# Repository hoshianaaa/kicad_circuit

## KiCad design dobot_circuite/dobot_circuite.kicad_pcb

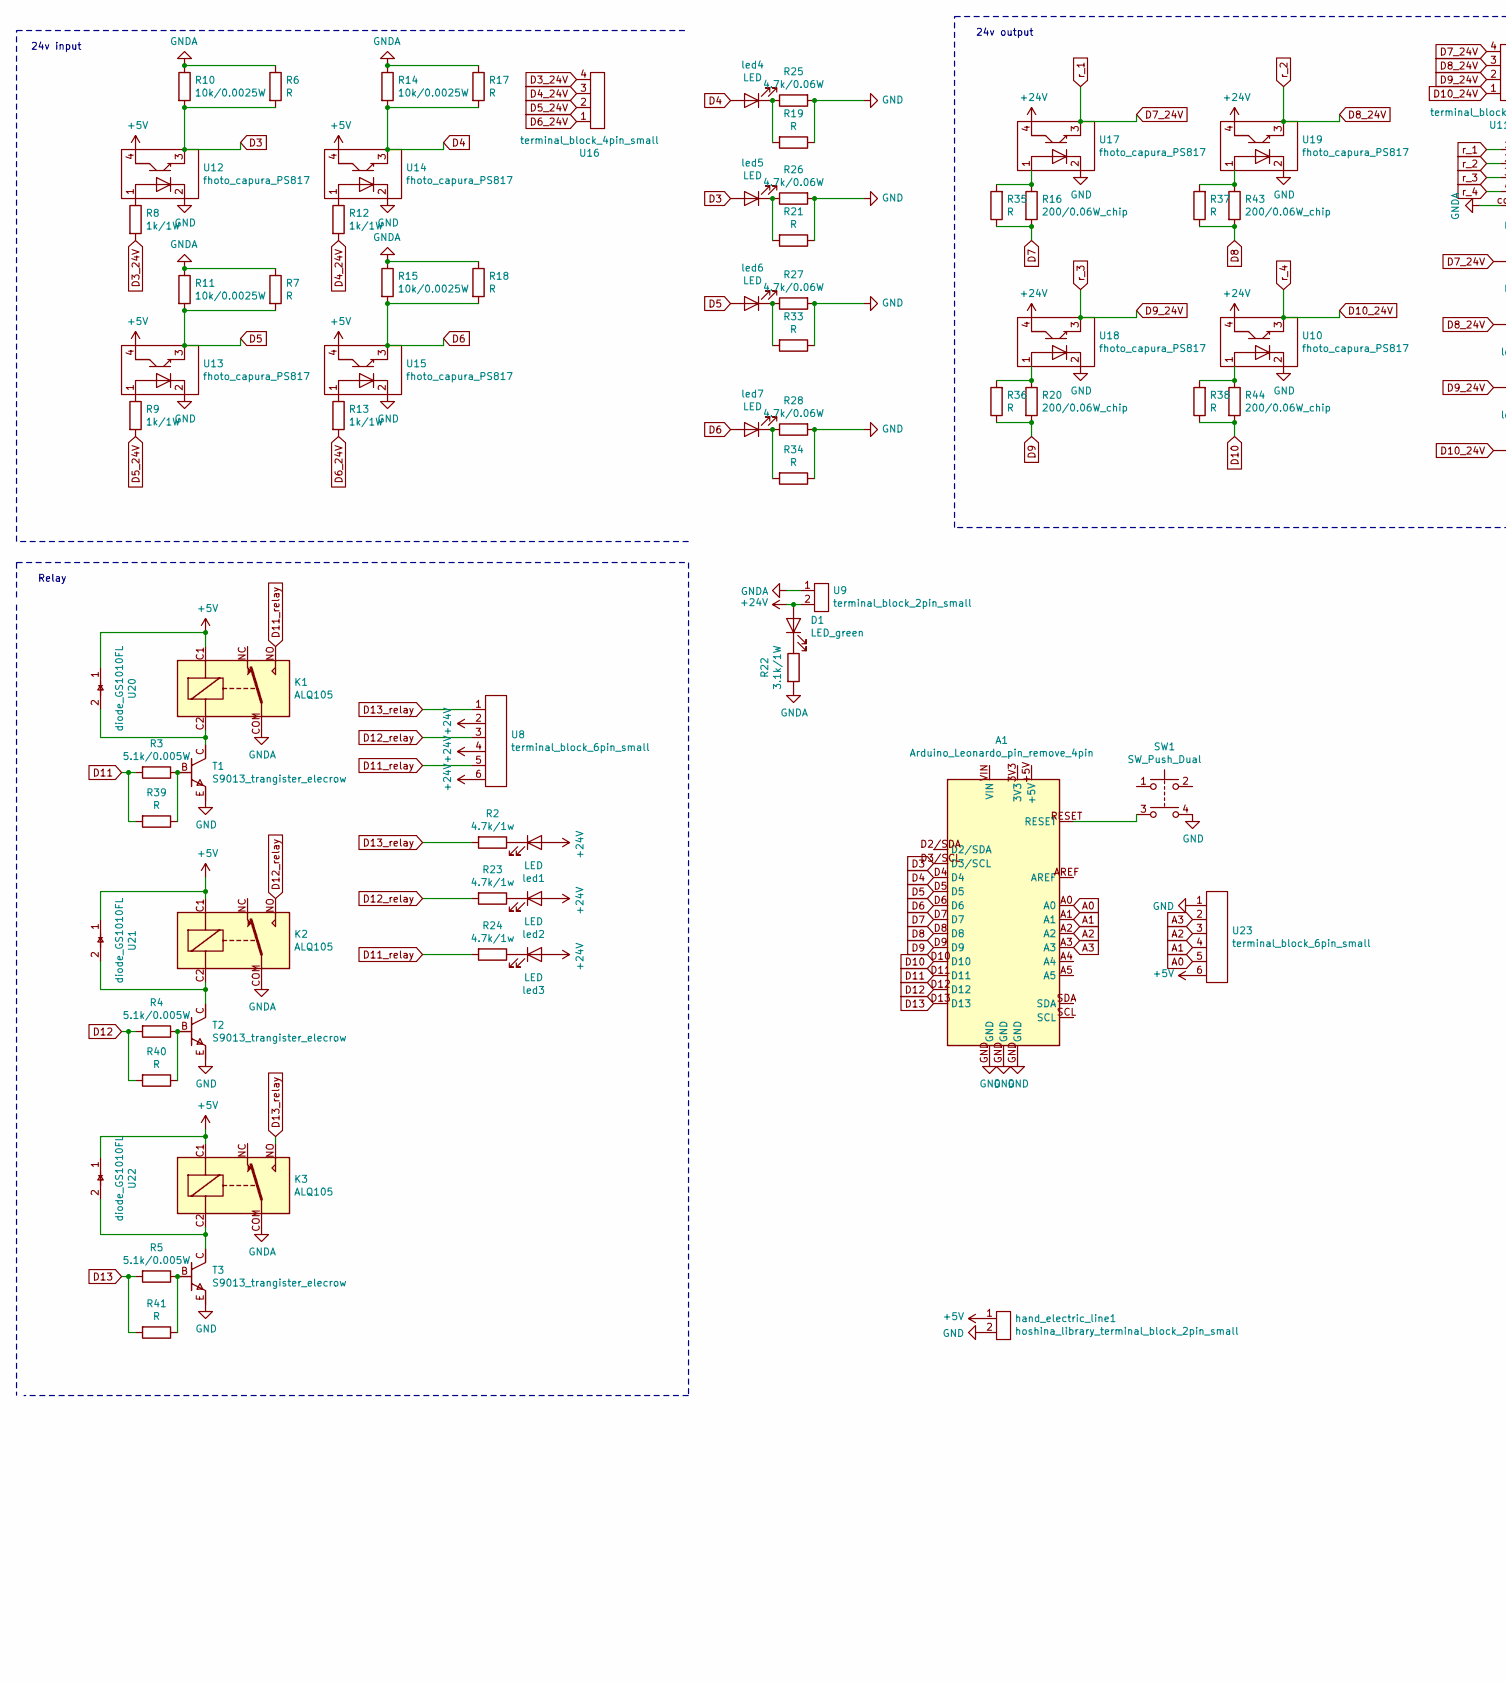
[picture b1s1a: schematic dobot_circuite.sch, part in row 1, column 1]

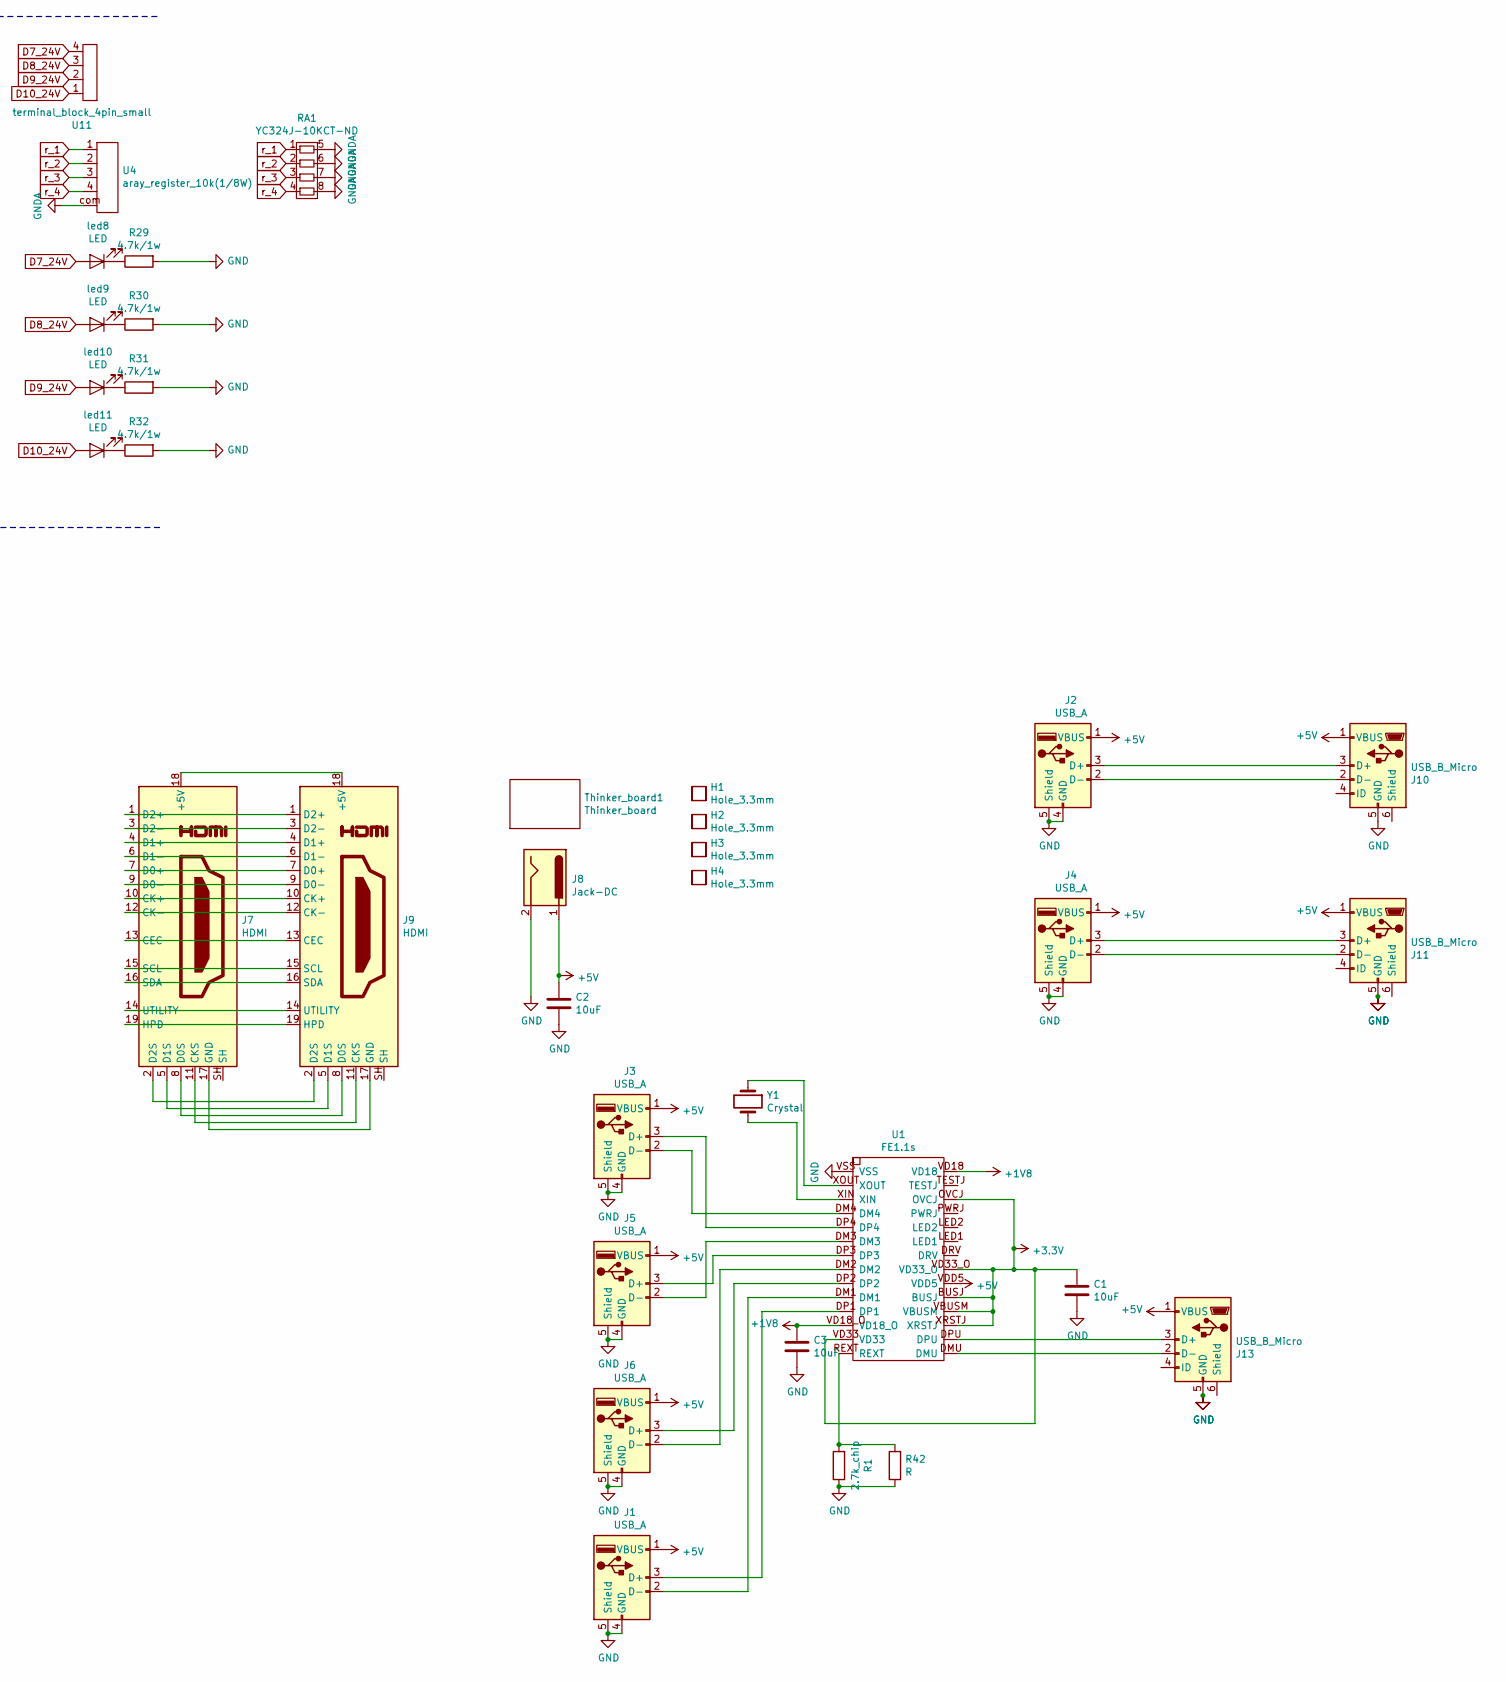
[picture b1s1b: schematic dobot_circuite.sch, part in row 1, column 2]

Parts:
A1: Arduino_Leonardo_pin_remove_4pin; arduino_leonard_remove_4pin
C1, C2, C3: 10uF; capa1608
D1: LED_green; LED_1608
H1, H2, H3, H4: Hole_3.3mm
J1, J2, J3, J4, J5, J6: USB_A; USB-A1
J7, J9: HDMI; HDMI_2000-1-1-20-00-BK
J8: Jack-DC; BarrelJack_Horizontal
J10, J11, J13: USB_B_Micro; USB_Micro-B_Molex_47346-0001
K1, K2, K3: ALQ105; ALQ105_akituki
R1: 2.7k_chip; register_0603
R2, R23, R24, R29, R30, R31, R32: 4.7k/1w; carbon_register
R3, R4, R5: 5.1k/0.005W; register_0603
R6, R7, R17, R18, R19, R21, R33, R34, R35, R36, R37, R38, R39, R40, R41, R42: R; carbon_register_1_6W_
R8, R9, R12, R13: 1k/1W; carbon_register
R10, R11, R14, R15: 10k/0.0025W; register_0603
R16, R20, R43, R44: 200/0.06W_chip; register_0603
R22: 3.1k/1W; carbon_register
R25, R26, R27, R28: 4.7k/0.06W; register_0603
RA1: YC324J-10KCT-ND
SW1: SW_Push_Dual; SW_TH_Tactile_Omron_B3F-10xx
T1, T2, T3: S9013_trangister_elecrow; S9013
Thinker_board1: Thinker_board
U1: FE1.1s
U4: aray_register_10k(1/8W); array_register
U8, U23: terminal_block_6pin_small
U9: terminal_block_2pin_small
U10, U12, U13, U14, U15, U17, U18, U19: fhoto_capura_PS817; fhoto_capra_PS817
U11, U16: terminal_block_4pin_small
U20, U21, U22: diode_GS1010FL
Y1: Crystal; Crystal_SMD_5032-2Pin_5.0x3.2mm
hand_electric_line1: hoshina_library_terminal_block_2pin_small; XH2_pin
led1, led2, led3, led4, led5, led6, led7, led8, led9, led10, led11: LED; LED_1608

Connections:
+1V8: C3.1, U1.VD18, U1.VD18_O
+3V3: C1.1, U1.BUSJ, U1.OVCJ, U1.VBUSM, U1.VD33, U1.VD33_O, U1.XRSTJ
+5V: C2.1, J1.1 (VBUS), J2.1 (VBUS), J3.1 (VBUS), J4.1 (VBUS), J5.1 (VBUS), J6.1 (VBUS), J8.1, J10.1 (VBUS), J11.1 (VBUS), J13.1 (VBUS), K1.C1, K2.C1, K3.C1, U1.VDD5, U12.4, U13.4, U14.4, U15.4, U20.1, U21.1, U22.1, U23.6, hand_electric_line1.1
+24V: D1.2 (A), U8.2, U8.4, U8.6, U9.2, U10.4, U17.4, U18.4, U19.4, led1.2 (A), led2.2 (A), led3.2 (A)
A0: A1.A0, U23.5
A1: A1.A1, U23.4
A2: A1.A2, U23.3
A3: A1.A3, U23.2
D3: A1.D3/SCL, R6.2, R10.2, U12.3, led5.2 (A)
D3_24V: R8.2, U16.4
D4: A1.D4, R14.2, R17.2, U14.3, led4.2 (A)
D4_24V: R12.2, U16.3
D5: A1.D5, R7.2, R11.2, U13.3, led6.2 (A)
D5_24V: R9.2, U16.2
D6: A1.D6, R15.2, R18.2, U15.3, led7.2 (A)
D6_24V: R13.2, U16.1
D7: A1.D7, R16.2, R35.1
D7_24V: RA1.1, U4.1, U11.4, U17.3, led8.2 (A)
D8: A1.D8, R37.1, R43.2
D8_24V: RA1.2, U4.2, U11.3, U19.3, led9.2 (A)
D9: A1.D9, R20.2, R36.1
D9_24V: RA1.3, U4.3, U11.2, U18.3, led10.2 (A)
D10: A1.D10, R38.1, R44.2
D10_24V: RA1.4, U4.4, U10.3, U11.1, led11.2 (A)
D11: A1.D11, R3.2, R39.2
D11_relay: K1.NO, R24.2, U8.5
D12: A1.D12, R4.2, R40.2
D12_relay: K2.NO, R23.2, U8.3
D13: A1.D13, R5.2, R41.2
D13_relay: K3.NO, R2.2, U8.1
GND: A1.GND, C1.2, C2.2, C3.2, J1.4 (GND), J1.5 (Shield), J2.4 (GND), J2.5 (Shield), J3.4 (GND), J3.5 (Shield), J4.4 (GND), J4.5 (Shield), J5.4 (GND), J5.5 (Shield), J6.4 (GND), J6.5 (Shield), J8.2, J10.5 (GND), J11.5 (GND), J13.5 (GND), R1.1, R19.1, R21.1, R25.2, R26.2, R27.2, R28.2, R29.2, R30.2, R31.2, R32.2, R33.1, R34.1, R42.1, SW1.4, T1.E, T2.E, T3.E, U1.VSS, U10.2, U12.2, U13.2, U14.2, U15.2, U17.2, U18.2, U19.2, U23.1, hand_electric_line1.2
GNDA: K1.COM, K2.COM, K3.COM, R6.1, R7.1, R10.1, R11.1, R14.1, R15.1, R17.1, R18.1, R22.2, RA1.5, RA1.6, RA1.7, RA1.8, U4.com, U9.1
unnamed: A1.RESET, SW1.3
unnamed: D1.1 (K), R22.1
unnamed: J1.2 (D-), U1.DM1
unnamed: J1.3 (D+), U1.DP1
unnamed: J3.2 (D-), U1.DM4
unnamed: J3.3 (D+), U1.DP4
unnamed: J5.2 (D-), U1.DM3
unnamed: J5.3 (D+), U1.DP3
unnamed: J6.2 (D-), U1.DM2
unnamed: J6.3 (D+), U1.DP2
unnamed: J7.1 (D2+), J9.1 (D2+)
unnamed: J7.2 (D2S), J9.2 (D2S)
unnamed: J7.3 (D2-), J9.3 (D2-)
unnamed: J7.4 (D1+), J9.4 (D1+)
unnamed: J7.5 (D1S), J9.5 (D1S)
unnamed: J7.6 (D1-), J9.6 (D1-)
unnamed: J7.7 (D0+), J9.7 (D0+)
unnamed: J7.8 (D0S), J9.8 (D0S)
unnamed: J7.9 (D0-), J9.9 (D0-)
unnamed: J7.10 (CK+), J9.10 (CK+)
unnamed: J7.11 (CKS), J9.11 (CKS)
unnamed: J7.12 (CK-), J9.12 (CK-)
unnamed: J7.13 (CEC), J9.13 (CEC)
unnamed: J7.14 (UTILITY), J9.14 (UTILITY)
unnamed: J7.15 (SCL), J9.15 (SCL)
unnamed: J7.16 (SDA), J9.16 (SDA)
unnamed: J7.17 (GND), J9.17 (GND)
unnamed: J7.18 (+5V), J9.18 (+5V)
unnamed: J7.19 (HPD), J9.19 (HPD)
unnamed: J2.2 (D-), J10.2 (D-)
unnamed: J2.3 (D+), J10.3 (D+)
unnamed: J4.2 (D-), J11.2 (D-)
unnamed: J4.3 (D+), J11.3 (D+)
unnamed: J13.2 (D-), U1.DMU
unnamed: J13.3 (D+), U1.DPU
unnamed: K1.C2, T1.C, U20.2
unnamed: K2.C2, T2.C, U21.2
unnamed: K3.C2, T3.C, U22.2
unnamed: R1.2, R42.2, U1.REXT
unnamed: R2.1, led1.1 (K)
unnamed: R3.1, R39.1, T1.B
unnamed: R4.1, R40.1, T2.B
unnamed: R8.1, U12.1
unnamed: R9.1, U13.1
unnamed: R12.1, U14.1
unnamed: R13.1, U15.1
unnamed: R16.1, R35.2, U17.1
unnamed: R19.2, R25.1, led4.1 (K)
unnamed: R20.1, R36.2, U18.1
unnamed: R21.2, R26.1, led5.1 (K)
unnamed: R23.1, led2.1 (K)
unnamed: R24.1, led3.1 (K)
unnamed: R27.1, R33.2, led6.1 (K)
unnamed: R28.1, R34.2, led7.1 (K)
unnamed: R29.1, led8.1 (K)
unnamed: R30.1, led9.1 (K)
unnamed: R31.1, led10.1 (K)
unnamed: R32.1, led11.1 (K)
unnamed: R37.2, R43.1, U19.1
unnamed: R38.2, R44.1, U10.1
unnamed: R5.1, R41.1, T3.B
unnamed: U1.XIN, Y1.2
unnamed: U1.XOUT, Y1.1

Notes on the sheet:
24v input
24v output
Relay

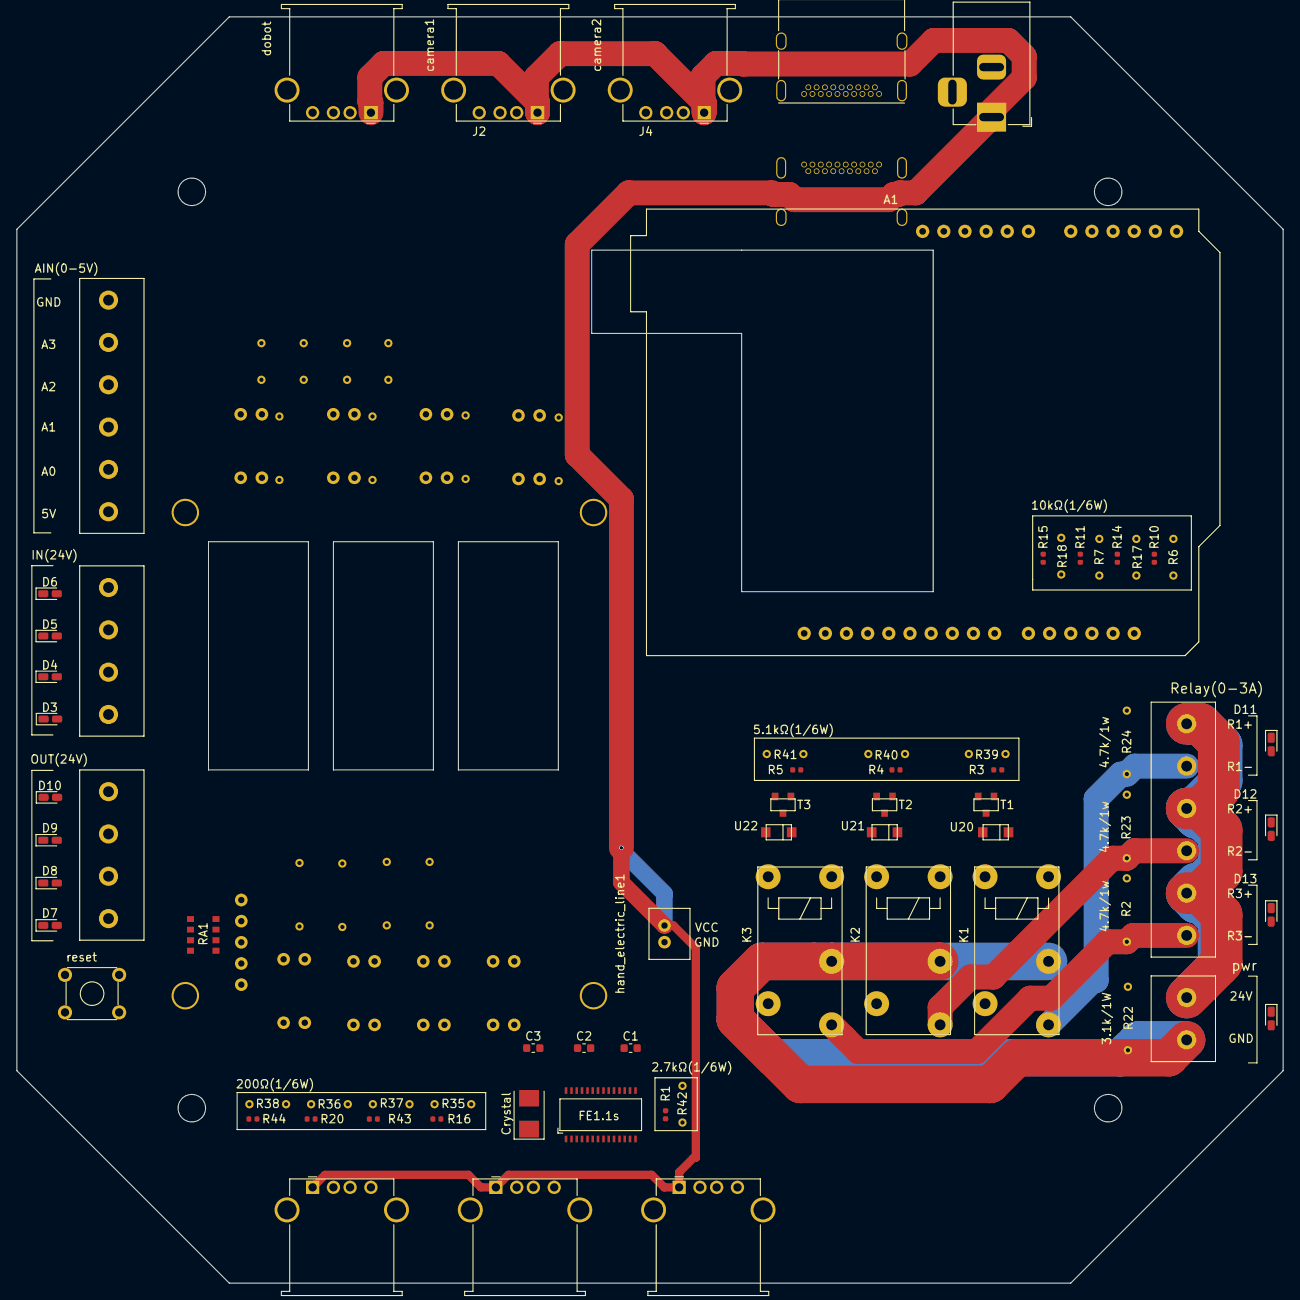
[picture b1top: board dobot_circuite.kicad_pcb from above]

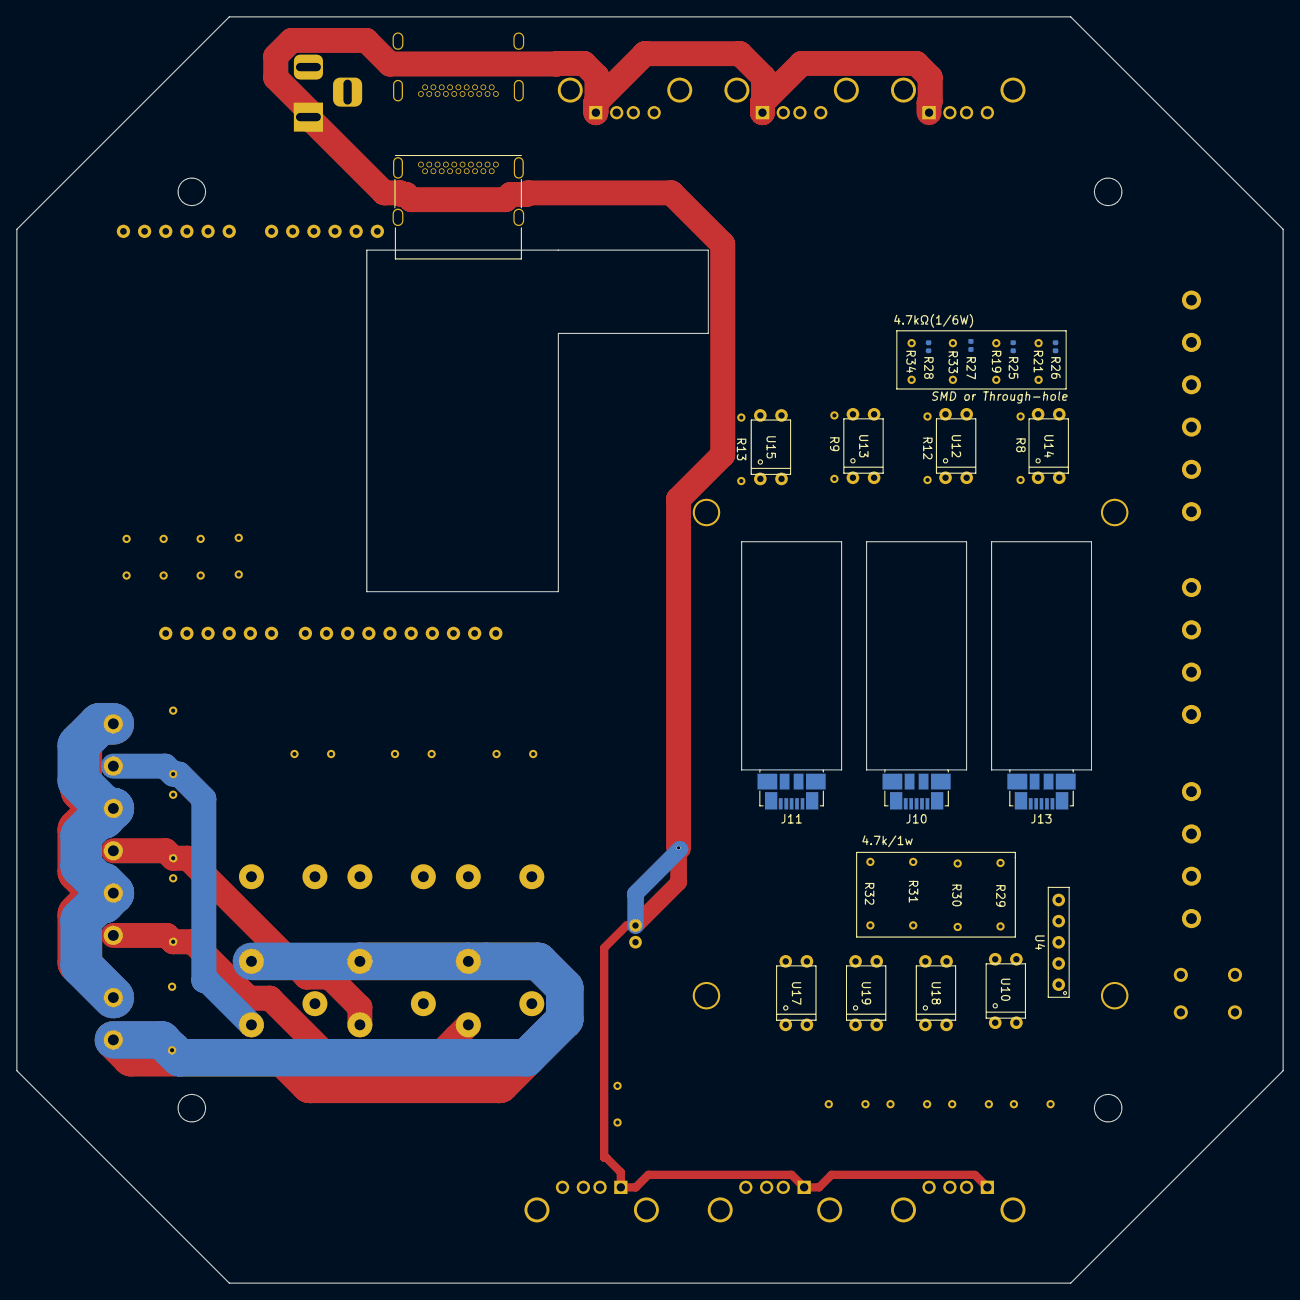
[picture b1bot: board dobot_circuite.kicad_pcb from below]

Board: 2 copper layers, 152.0 x 152.0 mm, 105 parts (29 on the bottom side), 95 nets.

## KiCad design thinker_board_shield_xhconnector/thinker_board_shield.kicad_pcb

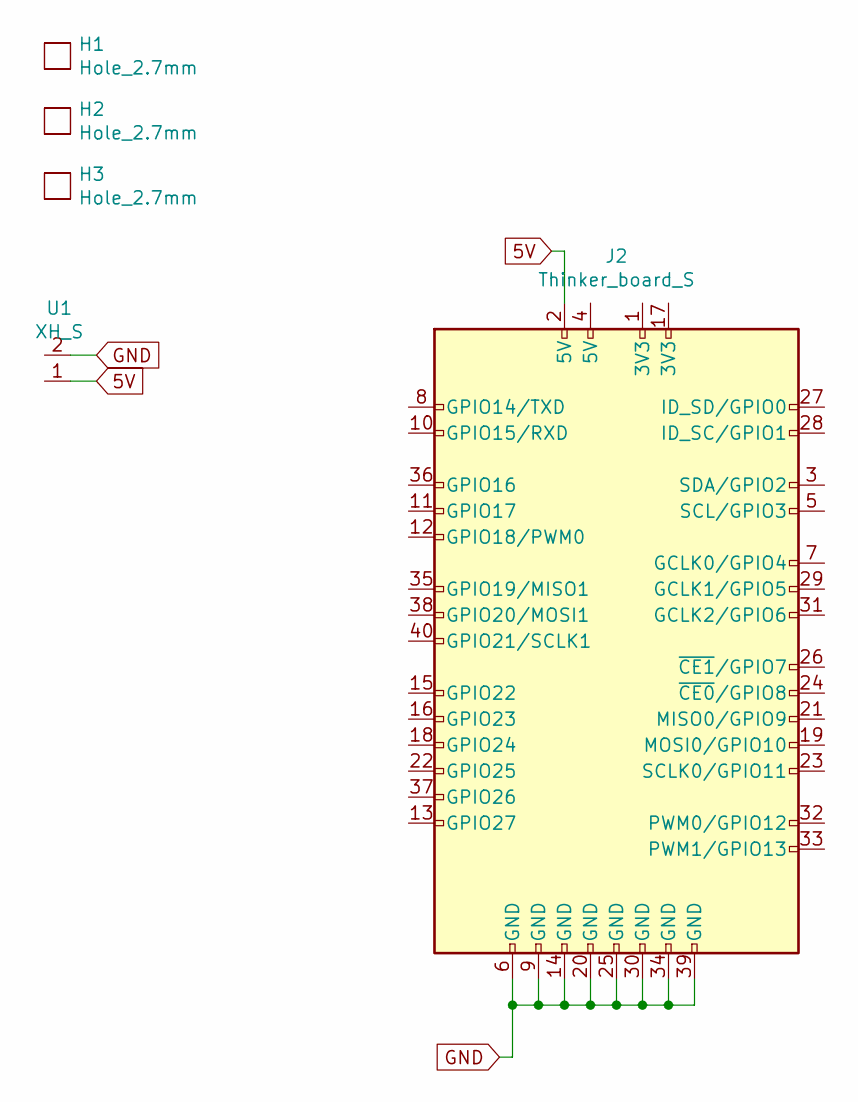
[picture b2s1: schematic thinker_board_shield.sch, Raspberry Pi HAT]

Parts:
H1, H2, H3: Hole_2.7mm
J2: Thinker_board_S; Thinker_board_pin
U1: XH_S; S2B-XH-A

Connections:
5V: J2.2 (5V), U1.1
GND: J2.6 (GND), J2.9 (GND), J2.14 (GND), J2.20 (GND), J2.25 (GND), J2.30 (GND), J2.34 (GND), J2.39 (GND), U1.2

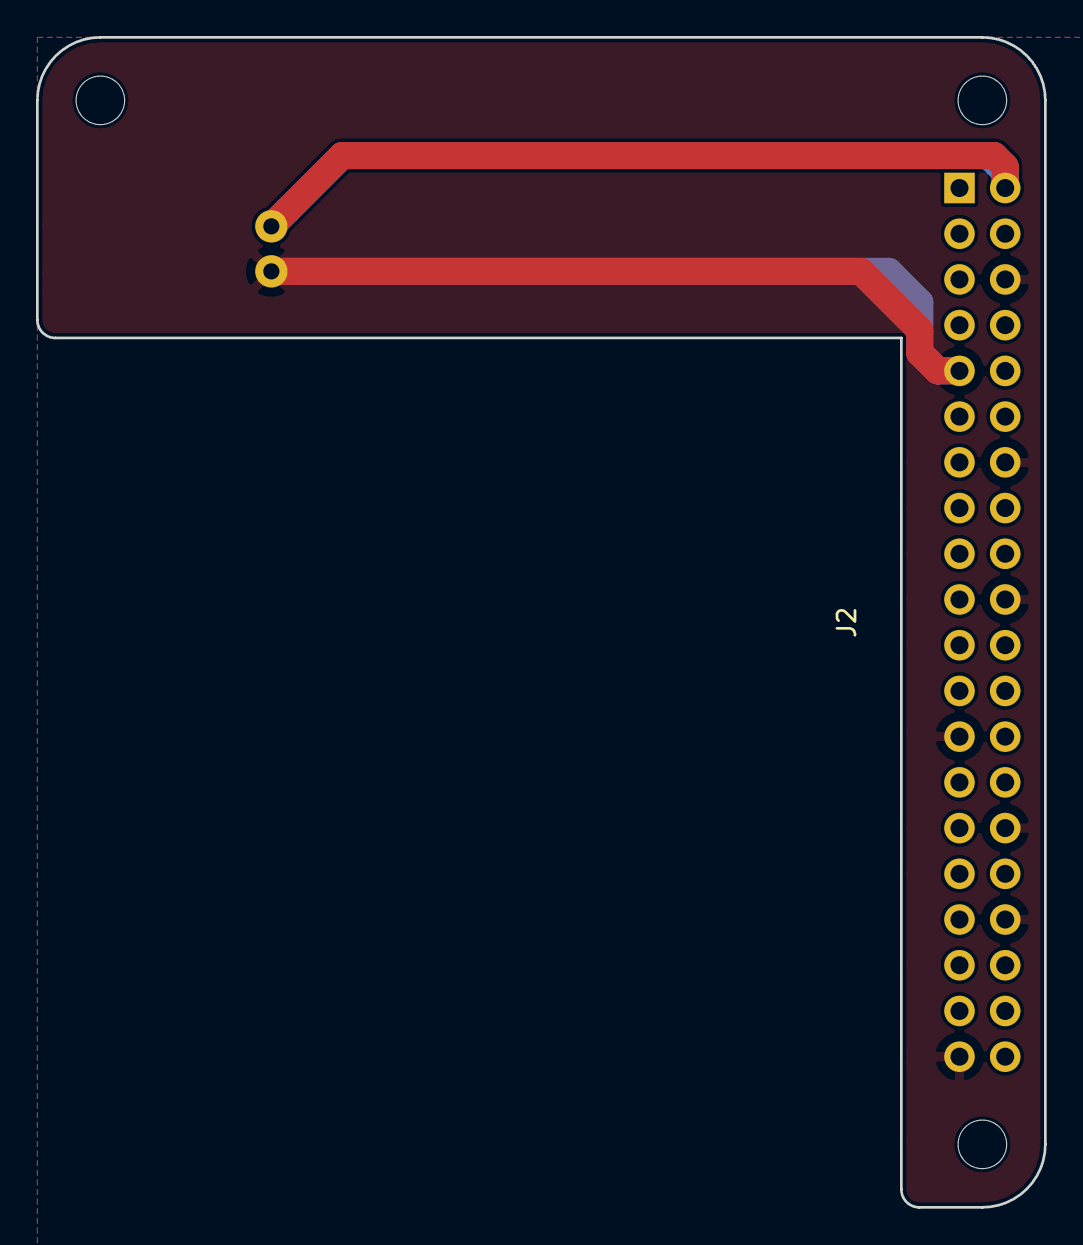
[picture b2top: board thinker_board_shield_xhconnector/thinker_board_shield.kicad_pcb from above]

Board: 4 copper layers, 56.0 x 65.0 mm, 5 parts (1 on the bottom side), 2 nets.

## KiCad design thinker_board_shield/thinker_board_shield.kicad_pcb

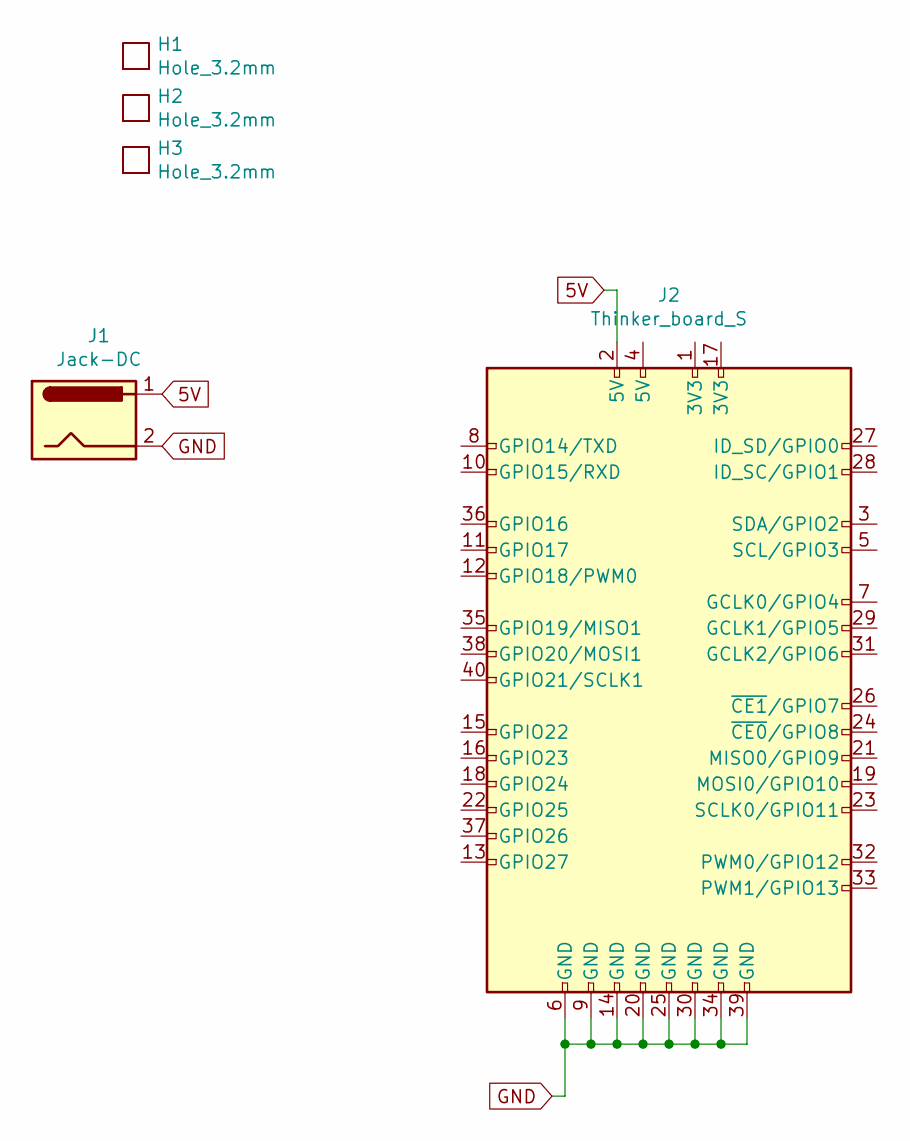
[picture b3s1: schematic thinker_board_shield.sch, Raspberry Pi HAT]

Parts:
H1, H2, H3: Hole_3.2mm
J1: Jack-DC; DCJ
J2: Thinker_board_S; Thinker_board_pin

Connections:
5V: J1.1, J2.2 (5V)
GND: J1.2, J2.6 (GND), J2.9 (GND), J2.14 (GND), J2.20 (GND), J2.25 (GND), J2.30 (GND), J2.34 (GND), J2.39 (GND)

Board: 4 copper layers, 5 parts (1 on the bottom side), 2 nets, no tracks yet.
